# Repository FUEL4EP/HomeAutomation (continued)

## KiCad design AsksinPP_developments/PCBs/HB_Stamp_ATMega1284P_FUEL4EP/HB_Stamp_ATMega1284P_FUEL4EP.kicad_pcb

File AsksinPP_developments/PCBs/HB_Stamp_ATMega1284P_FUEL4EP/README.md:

# HB_Stamp_ATMega1284P_FUEL4EP  

**kleine Platine für DIY AsksinPP Geräte mit I2C und 3x IO-Pins**
- Platinenmaße 22 mm x 40 mm
- Platinendicke: 0.8 mm (bitte nicht ändern, da Antenne sonst nicht funktioniert)
- I2C-Steckerleistenanschluss für I2C-Module
- 3 weitere IO-Pins anschließbar: PC4, PA5, PB3
- optionaler Hochsetzwandler 1,2V .. 1,5V auf 3,3V mit TI TPS61221 für Betrieb mit 1x Batterie
- Versorgung mit 1x AA-Batterie (1,5V) oder 1x NiMH-Akkumulator (1,2V) möglich
- alternativ Versorgung mit 2x AA Batterien ohne Hochsetzwandler
- [integrierte 868 MHz PCB Antenne](https://www.ti.com/lit/an/swra416/swra416.pdf)
- 10 mm x 10 mm kleines Sendemodul [eByte E07 900MM10S](https://datasheet.lcsc.com/lcsc/2305061757_Chengdu-Ebyte-Elec-Tech-E07-900MM10S_C5844212.pdf) auf Platinenrückseite von Hand verlötet
- SMD TQFP-44 [ATMega1284P](https://ww1.microchip.com/downloads/en/DeviceDoc/doc8059.pdf) mit 128kByte Programmspeicher, 16kByte SRAM, 4kByte EEPROM
	+ ohne externen Quarz, Betrieb mit 8 MHz internem RC-Oszillator
		+ bitte dies unbedingt bei der Programmierung von Fuses berücksichtigen!
- Programmierung und Serial Monitor mittels 2,54 mm Pogo-Pin-Adapter, Anschlüsse sind an der gleichen Stelle auf gegenüberliegenden Platinenseiten
- alle SMD Bausteine sind mit dem JLCPCB SMT Bestückungsservice kostengünstig und qualitativ hochwertig bestückbar
- die JLCPCB Assemblierung des Funkmoduls eByte E07-900MM10S geht nur als sehr teures Standard PCBA, daher wird eine Verlötung von Hand empfohlen

- Bilder der bei JLCPCB gefertigten und assemblierten Prototypplatine V1.2

- das eByte E07 900MM10S Sendemodul muss aus Kostengründen von Hand aufgelötet werden
- - V1.2 der Platine hatte noch falsche I2C-Pullup-Widerstände, die ausgelötet werden mussten
- in der aktuellen Version auf Github ist dieser Fehler behoben
- zusätzlich wurden die Anschlussflächen für den Pogo-Pin_Adapter als Ring ausgeführt, damit die Pogo-Pins besser zu zentrieren sind

## Credits

- mein besonderer Dank geht an papa für [AsksinPP](https://github.com/pa-pa/AskSinPP) und [Jérôme jp112sdl](https://github.com/jp112sdl) für die stete Unterstützung.

## Platine V1.2 wurde bei JLCPCB gefertigt und erfolgreich validiert

- entwickelt mit KiCAD 6.0.11
- V1.2 hatte noch falsche I2C-Pullup-Widerstände, die ausgelötet werden mussten
- in der aktuellen Version der Platine auf Github ist dieser Fehler behoben

## Eigenschaften

- kompletter Datensatz für KiCAD 8 auf Github verfügbar:
    + 'git clone https://github.com/FUEL4EP/HomeAutomation.git' oder als [ZIP-Datei](https://github.com/FUEL4EP/HomeAutomation/archive/refs/heads/master.zip)
    + die Platinendaten sind dann unter 'HomeAutomation/AsksinPP_developments/PCBs/HB_Stamp_ATMega1284P_FUEL4EP' direkt mit KiCAD aufrufbar
- neue Eigenschaften:
    + SMD Bestückung, wo möglich
    + alle SMD Bausteine sind mit dem JLCPCB SMT Bestückungsservice kostengünstig und qualitativ hochwertig bestückbar
    + JLCPCB BOM and CPL Dateien für SMT Service werden [bereitgestellt](./jlcpcb/production_files)
    + die AsksinPP Reset- und Config-Taster sind aus Platzgründen als Platinenjumper ausgeführt. Bitte geeignet kurz überbrücken, z.B. mit einem Schraubendreher

### Benötigte Bauteile:

- bei Anspruchsnahme des SMT Bestückungsservice von JLCPCB ist nur noch das Funkmodul eByte E07-900MM10S von Hand auf die Platinenrückseite zu löten
- die JLCPCB Assemblierung des Funkmoduls eByte E07-900MM10S geht nur als sehr teures Standard PCBA, daher wird eine Verlötung von Hand empfohlen

### Passende AsksinPP Projekte von FUEL4EP
   + z.B. [HB-UNI-Sensor1-THPD-SHT45_BME280](https://github.com/FUEL4EP/HomeAutomation/tree/master/AsksinPP_developments/sketches/HB-UNI-Sensor1-THPD-SHT45_BME280)
   
### Aufbauhinweise

- es wird dringend angeraten, als ersten Schritt der Inbetriebnahme einen Frequenztest durchzuführen. Vorher bitte die Fuses mit avrdude setzen.

## Setzen der Fuses des ATMega1284P Mikrokontrollers

- **nie die Fuses auf einen externen Quarzoszillator / Resonator umschalten!**
- ein passender avrdude Skript zum Lesen und korrekten Setzen der Fuses ist [hier](./avrdude)

## Prüfwerkzeuge

- ein Frequenztest ist [hier](./FreqTest_1284P/)

### Anschluss eines FTDI Debuggers und/oder ISP-Programmiergeräts

- Anschluss über 6-Pin 2,54 mm Pogo-Pin-Adapter auf der Platinenoberseite (FTDI Debugger) bzw. der Platinenunterseite (ISP Programmierer)
- bitte vor Anschluss prüfen, dass die korrekte Platinenseite verwendet wird.
- bitte die Beschriftung beachten und vor dem Anlegen eines Pogo-Pin-Adapters querprüfen!
- den ISP-Programmierer auf 3,3V Programmierspannung einstellen.
- zuerst die Fuses mit avrdude setzen
- Bild des Pogo-Pin_Adapters für den FTDI Debugger:

- Bild des Pogo-Pin_Adapters für den Diamex Prog S2 ISP Programmieradapter:

- gegebenenfalls muss die untere Acrylanpressplatte des Pogo-Pin_Adapters z.B. mit einem Dremel verkleinert werden, damit sie an HB_STAMP_ATMEGA1284P_FUEL4EP angebracht werden kann:

- eine Anleitung zur Nutzung des eine Diamex Prog S2 Programmierers unter Linux ist [hier](https://github.com/FUEL4EP/HomeAutomation/tree/master/AsksinPP_developments/HowTos/ISP%20Programmer/Diamex%20Prog-S2) beschrieben

### Passendes Gehäuse
- ein 3D druckbares Gehäuse ist [hier](./case_HB-UNI-Sensor1-THPD-SHT45_BME280/) zu finden  
- ein parametrisierbares OpenSCAD Modell ist beigefügt

### Hinweise
* Achtung: Kein Überspannungsschutz oder Verpolungsschutz vorhanden
* bei der Nutzung des JLCPCB SMT Bestückungsservice ist darauf zu achten, dass **alle** benötigten SMD Bauteile als im Lager **verfügbar** angezeigt werden. Sonst bitte **NICHT** bestellen!

### KiCAD Plugin
- für die Erzeugung der JLCPCB Produktionsdaten wurde das Plugin [KiCAD JLCPCB tools](https://github.com/bouni/kicad-jlcpcb-tools) verwendet.

## Bestellen von Platinen

- die Platine kann direkt bei JLCPCB bestellt und dort auch assembliert werden
- die notwendigen Produktionsdaten stehen [hier](./jlcpcb/production_files/)
- die folgenden Bauteile müssen [vorab bei JLCPCB bestellt werden](https://jlcpcb.com/help/article/53-what-is-jlcpcb-parts-pre-order-service):
	+ [TI TPS61221DCKT](https://jlcpcb.com/parts/componentSearch?searchTxt=TPS61221) (zur Zeit teuer, ist aber meist billiger als zuerst angegeben)
	+ Murata LQH3NPN4R7MMEL 4.7 uH SMD Induktivität
- die JLCPCB Assemblierung des Funkmoduls eByte E07-900MM10S geht nur als das sehr teure Standard PCBA, daher wird eine Verlötung von Hand empfohlen

## Disclaimer

-   die Nutzung der hier veröffentlichten Inhalte erfolgt vollständig auf eigenes Risiko und ohne jede Gewähr.

## Versionsverlauf

-   V1.0   13. Jan 2024: Initiale Vorabfreigabe
-	V1.1	   15. Jan 2024: Änderung der I2C Stiftbelegung
-	V1.2   21. Jan 2024: Drehen der PogoPin-Anschlüsse; Änderung von LCSC-Nummern für bessere Verfügbarkeit
-	V1.3   08. Feb 2024: Fix der I2C Pull-Up Widerstände
-	L V1.4 14. Feb 2024: Pogo-Pin Pads in Ringform
-	L V1.5 29. Sep 2024: Migration zu KiCAD 8
-	S V1.4 29. Sep 2024: Migration zu KiCAD 8
- 	KiCad Schaltplan-Editor   Version: 8.0.5-8.0.5-0~ubuntu22.04.1, release build unter Kubuntu22.04.1
- 	KiCad Leiterplatteneditor Version: 8.0.5-8.0.5-0~ubuntu22.04.1, release build unter Kubuntu22.04.1
- 	PCB Version 1.5
- 	Schematics  1.4

## Lizenz 

**Creative Commons BY-NC-SA**<br>
Give Credit, NonCommercial, ShareAlike

<br />This work is licensed under a <a rel="license" href="http://creativecommons.org/licenses/by-nc-sa/4.0/">Creative Commons Attribution-NonCommercial-ShareAlike 4.0 International License</a>.

-EOF

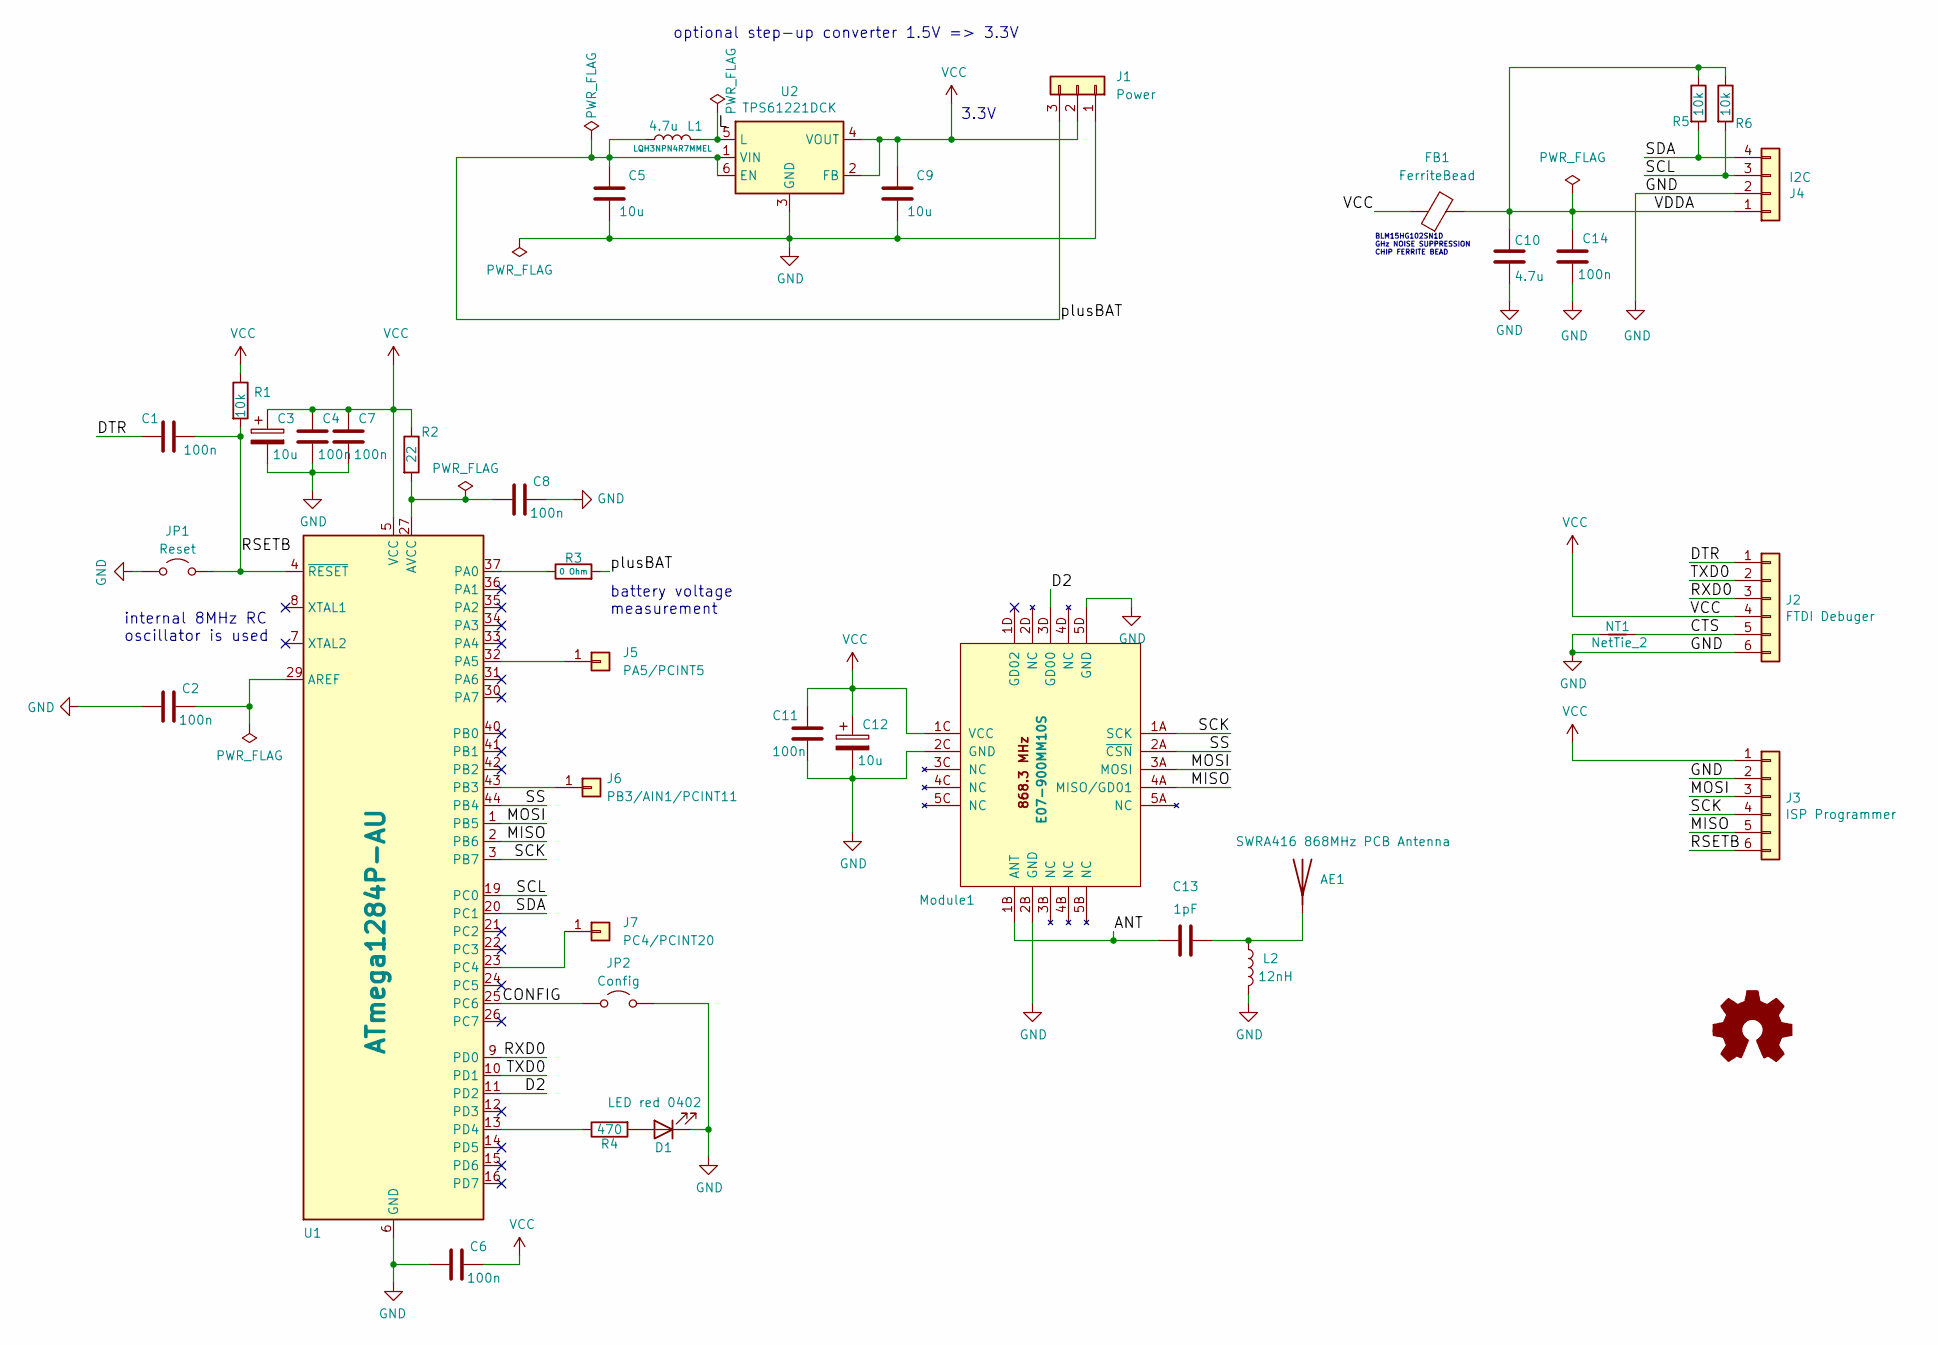
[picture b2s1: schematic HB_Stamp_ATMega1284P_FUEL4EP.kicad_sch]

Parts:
AE1: SWRA416 868MHz PCB Antenna; Texas_SWRA416_868MHz_915MHz
C1, C2, C4, C6, C7, C8, C11, C14: 100n; C_0402_1005Metric; LCSC C1525
C3, C12: 10u; C_0402_1005Metric; LCSC C15525
C5, C9: 10u; C_0805_2012Metric; LCSC C15850
C10: 4.7u; C_0402_1005Metric; LCSC C23733
C13: 1pF; C_0402_1005Metric; LCSC C72134
D1: LED red 0402; LED_0402_1005Metric; LCSC C273598
FB1: FerriteBead; L_0402_1005Metric; LCSC C76889
J1: Power; PinHeader_1x03_P2.54mm_Vertical
J2: FTDI Debuger; PogoPinHeader_SMD_1x06_P2.54mm_Vertical
J3: ISP Programmer; PogoPinHeader_SMD_1x06_P2.54mm_Vertical
J4: I2C; PinHeader_1x04_P2.54mm_Vertical
J5: PA5/PCINT5; PinHeader_1x01_P2.54mm_Vertical
J6: PB3/AIN1/PCINT11; TestPoint_Pad_1.0x1.0mm
J7: PC4/PCINT20; PinHeader_1x01_P2.54mm_Vertical
JP1: Reset; SolderJumper-2_P1.3mm_Open_Pad1.0x1.5mm
JP2: Config; SolderJumper-2_P1.3mm_Open_Pad1.0x1.5mm
L1: 4.7u; FUEL4EP_Inductor_SMD_1; LCSC C576538
L2: 12nH; L_0402_1005Metric; LCSC C2043991
LOGO1: Logo_Open_Hardware_Small; CC-BY-ND-SA
Module1: E07-900MM10S; eByte_E07-900MM10S; LCSC C5844212
NT1: NetTie_2; NetTie-2_SMD_Pad0.5mm
R1, R5, R6: 10k; R_0402_1005Metric; LCSC C25744
R2: 22; R_0402_1005Metric; LCSC C23345
R3: 0 Ohm; R_0402_1005Metric; LCSC C17168
R4: 470; R_0402_1005Metric; LCSC C25117
U1: ATmega1284P-AU; TQFP-44_10x10mm_P0.8mm; LCSC C33575
U2: TPS61221DCK; Texas_R-PDSO-G6; LCSC C2865756

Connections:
/ANT: C13.1, Module1.1B (ANT)
/CONFIG: JP2.1 (A), U1.25 (PC6)
/CTS: J2.5, NT1.2
/D2: Module1.3D (GD00), U1.11 (PD2)
/DTR: C1.1, J2.1
/L: L1.2, U2.5 (L)
/MISO: J3.5, Module1.4A (MISO/GD01), U1.2 (PB6)
/MOSI: J3.3, Module1.3A (MOSI), U1.1 (PB5)
/RSETB: C1.2, J3.6, JP1.2 (B), R1.2, U1.4 (~RESET)
/RXD0: J2.3, U1.9 (PD0)
/SCK: J3.4, Module1.1A (SCK), U1.3 (PB7)
/SCL: J4.3, R6.2, U1.19 (PC0)
/SDA: J4.4, R5.2, U1.20 (PC1)
/SS: Module1.2A (~CSN), U1.44 (PB4)
/TXD0: J2.2, U1.10 (PD1)
/VDDA: C10.1, C14.1, FB1.2, J4.1, R5.1, R6.1
/plusBAT: C5.1, J1.3, L1.1, R3.2, U2.1 (VIN), U2.6 (EN)
GND: C2.1, C3.2, C4.2, C5.2, C6.1, C7.2, C8.2, C9.2, C10.2, C11.2, C12.2, C14.2, D1.1 (K), J1.1, J2.6, J3.2, J4.2, JP1.1 (A), JP2.2 (B), L2.2, Module1.2B (GND), Module1.2C (GND), Module1.5D (GND), NT1.1, U1.6 (GND), U1.18 (GND), U1.28 (GND), U1.39 (GND), U2.3 (GND)
unnamed: AE1.1 (A), C13.2, L2.1
unnamed: D1.2 (A), R4.2
unnamed: J5.1, U1.32 (PA5)
unnamed: J6.1, U1.43 (PB3)
unnamed: J7.1, U1.23 (PC4)
unnamed: C2.2, U1.29 (AREF)
unnamed: C8.1, R2.2, U1.27 (AVCC)
unnamed: R3.1, U1.37 (PA0)
unnamed: R4.1, U1.13 (PD4)
VCC: C3.1, C4.1, C6.2, C7.1, C9.1, C11.1, C12.1, FB1.1, J1.2, J2.4, J3.1, Module1.1C (VCC), R1.1, R2.1, U1.5 (VCC), U1.17 (VCC), U1.38 (VCC), U2.2 (FB), U2.4 (VOUT)

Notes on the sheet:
battery voltage measurement
internal 8MHz RC oscillator is used
BLM15HG102SN1D GHz NOISE SUPPRESSION CHIP FERRITE BEAD
3.3V
optional step-up converter 1.5V => 3.3V

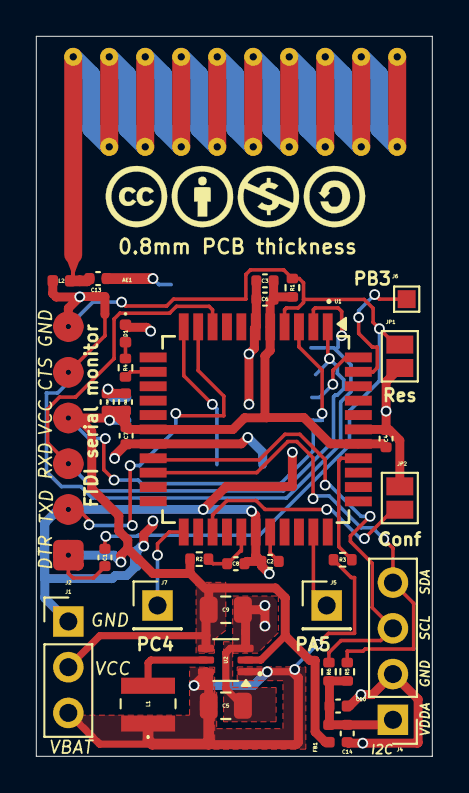
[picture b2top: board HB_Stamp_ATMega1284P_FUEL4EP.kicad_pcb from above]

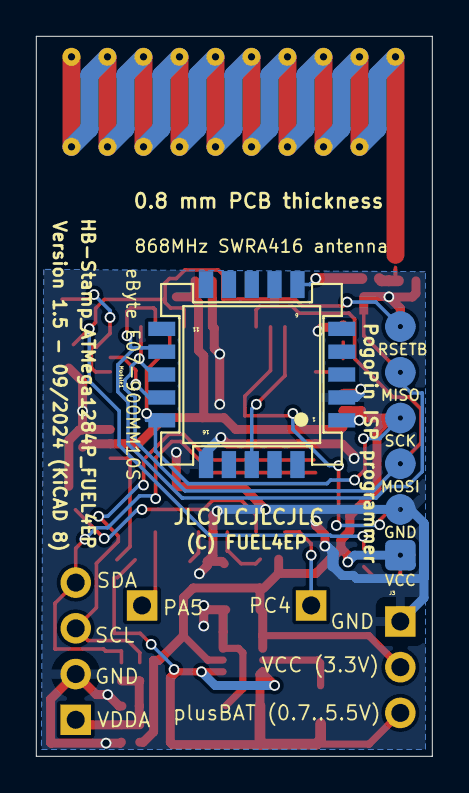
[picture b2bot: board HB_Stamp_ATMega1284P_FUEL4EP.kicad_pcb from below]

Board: 2 copper layers, 22.0 x 40.0 mm, 39 parts (2 on the bottom side), 28 nets.

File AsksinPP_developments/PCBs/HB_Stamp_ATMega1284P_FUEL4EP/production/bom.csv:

Designator,Footprint,Quantity,Value,LCSC Part #
AE1,Texas_SWRA416_868MHz_915MHz,1,SWRA416 868MHz PCB Antenna,
"C1, C11, C14, C2, C4, C6, C7, C8",0402,8,100n,C1525
C10,0402,1,4.7u,C23733
"C12, C3",0402,2,10u,C15525
C13,0402,1,1pF,C72134
"C5, C9",0805,2,10u,C15850
D1,0402,1,LED red 0402,C273598
FB1,0402,1,FerriteBead,C76889
J1,PinHeader_1x03_P2.54mm_Vertical,1,Power,
J2,PogoPinHeader_SMD_1x06_P2.54mm_Vertical,1,FTDI Debuger,
J3,PogoPinHeader_SMD_1x06_P2.54mm_Vertical,1,ISP Programmer,
J4,PinHeader_1x04_P2.54mm_Vertical,1,I2C,
J5,PinHeader_1x01_P2.54mm_Vertical,1,PA5/PCINT5,
J6,TestPoint_Pad_1.0x1.0mm,1,PB3/AIN1/PCINT11,
J7,PinHeader_1x01_P2.54mm_Vertical,1,PC4/PCINT20,
JP1,SolderJumper-2_P1.3mm_Open_Pad1.0x1.5mm,1,Reset,
JP2,SolderJumper-2_P1.3mm_Open_Pad1.0x1.5mm,1,Config,
L1,FUEL4EP_Inductor_SMD_1,1,4.7u,C576538
L2,0402,1,12nH,C2043991
Module1,eByte_E07-900MM10S,1,E07-900MM10S,C5844212
"R1, R5, R6",0402,3,10k,C25744
R2,0402,1,22,C23345
R3,0402,1,0 Ohm,C17168
R4,0402,1,470,C25117
U1,TQFP-44_10x10mm_P0.8mm,1,ATmega1284P-AU,C33575
U2,Texas_R-PDSO-G6,1,TPS61221DCK,C2865756

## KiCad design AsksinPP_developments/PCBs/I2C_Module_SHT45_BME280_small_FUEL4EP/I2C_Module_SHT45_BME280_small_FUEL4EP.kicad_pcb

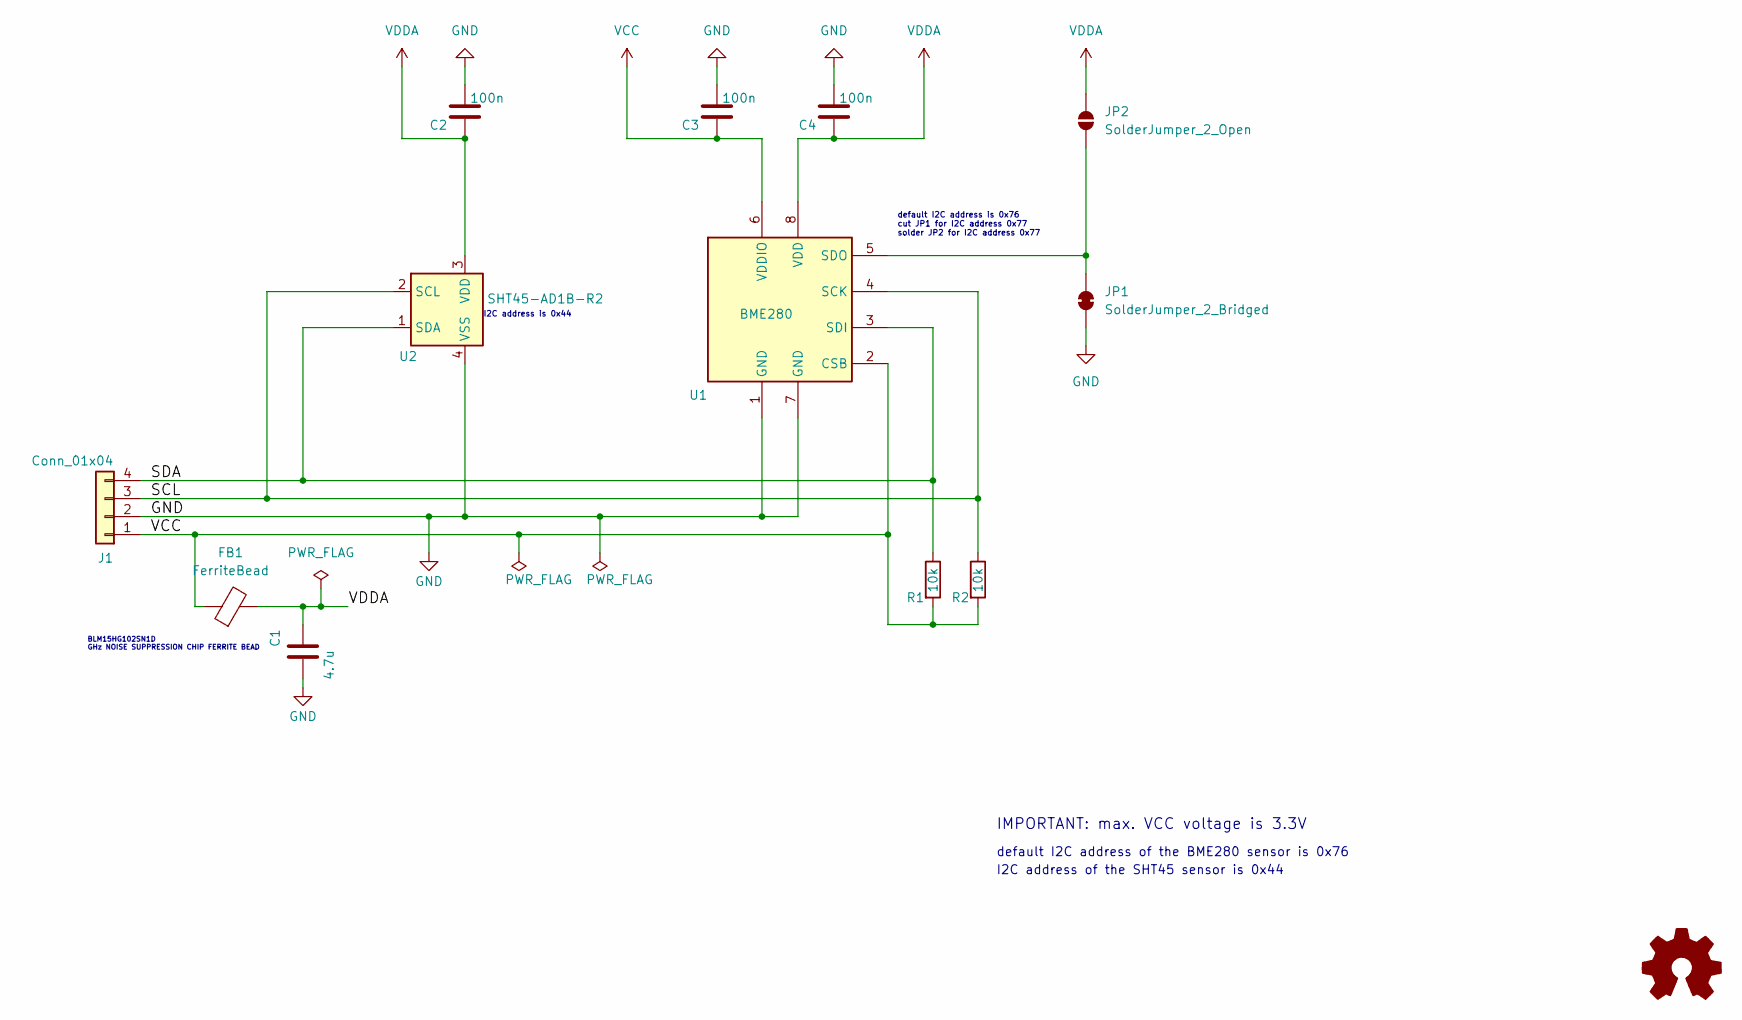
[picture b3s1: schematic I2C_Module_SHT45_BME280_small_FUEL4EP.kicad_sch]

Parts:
C1: 4.7u; C_0603_1608Metric; LCSC C19666
C2, C3, C4: 100n; C_0603_1608Metric; LCSC C14663
FB1: FerriteBead; L_0402_1005Metric; LCSC C76889
J1: Conn_01x04; PinHeader_1x04_P2.54mm_Vertical
JP1: SolderJumper_2_Bridged; SolderJumper-2_P1.3mm_Bridged_Pad1.0x1.5mm
JP2: SolderJumper_2_Open; SolderJumper-2_P1.3mm_Open_Pad1.0x1.5mm
LOGO1: Logo_Open_Hardware_Small; CC-BY-ND-SA
R1, R2: 10k; R_0402_1005Metric; LCSC C25744
U1: BME280; Bosch_LGA-8_2.5x2.5mm_P0.65mm_ClockwisePinNumbering; LCSC C92489
U2: SHT45-AD1B-R2; Sensirion_DFN-4_1.5x1.5mm_P0.8mm_SHT4x_NoCentralPad; LCSC C5221601

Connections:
/SCL: J1.3, R2.1, U1.4 (SCK), U2.2 (SCL)
/SDA: J1.4, R1.1, U1.3 (SDI), U2.1 (SDA)
GND: C1.2, C2.1, C3.1, C4.1, J1.2, JP1.1 (A), U1.1 (GND), U1.7 (GND), U2.4 (VSS)
unnamed: JP1.2 (B), JP2.1 (A), U1.5 (SDO)
VCC: C3.2, FB1.1, J1.1, R1.2, R2.2, U1.2 (CSB), U1.6 (VDDIO)
VDDA: C1.1, C2.2, C4.2, FB1.2, JP2.2 (B), U1.8 (VDD), U2.3 (VDD)

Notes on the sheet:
cut JP1 for I2C address 0x77
I2C address is 0x44
BLM15HG102SN1D GHz NOISE SUPPRESSION CHIP FERRITE BEAD
solder JP2 for I2C address 0x77
default I2C address of the BME280 sensor is 0x76
I2C address of the SHT45 sensor is 0x44
default I2C address is 0x76
IMPORTANT: max. VCC voltage is 3.3V

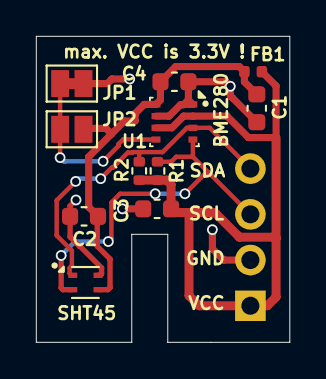
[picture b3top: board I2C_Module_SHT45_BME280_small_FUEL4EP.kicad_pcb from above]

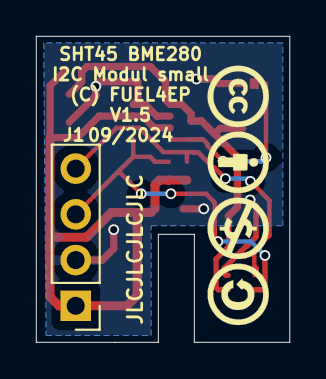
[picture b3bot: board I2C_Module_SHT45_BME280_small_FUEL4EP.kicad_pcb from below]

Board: 2 copper layers, 14.1 x 17.0 mm, 13 parts (2 on the bottom side), 6 nets.

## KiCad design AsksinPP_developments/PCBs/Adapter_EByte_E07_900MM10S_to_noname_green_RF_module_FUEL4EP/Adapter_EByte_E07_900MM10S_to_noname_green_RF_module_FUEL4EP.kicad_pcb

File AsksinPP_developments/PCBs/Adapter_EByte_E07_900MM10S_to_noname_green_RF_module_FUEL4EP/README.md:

# Adapter_EByte_E07_900MM10S_to_noname_green_RF_module_FUEL4EP  

## Ersatz für das NoName grüne 868,3 MHz Funkmodul

- Da das NoName grüne 868,3 MHz Modul häufig eine schlechte Qualität hat, wurde dieser Adapter als Ersatz entworfen. Es wird ein verfügbares, qualitativ hochwertiges EByte E07 900MM10S Funkmodul mit Abschirmkappe verbaut.

## Adapter für 868,3 MHz Funkmodul Ebyte E07 900MM10S auf das NoName grüne 868,3 MHz Funkmodul

- Infos zu AsksinPP sind [hier](https://asksinpp.de) und [hier](https://asksinpp.de/Grundlagen/01_hardware.html#verdrahtung) zu finden

## Umbenennung

- der PCB Name wurde in Version 1.1 von 'Adapter_noname_green_RF_module_to_Ebyte_E07_868MS10_FUEL4EP' in 'Adapter_EByte_E07_900MM10S_to_noname_green_RF_module_FUEL4EP' umbenannt

## Platinenmaße

- Breite: 19,2 mm
- Weite: 17 mm

## Stromlaufplan

- ist [hier](./Schematics/Adapter_EByte_E07_900MM10S_to_noname_green_RF_module_FUEL4EP.pdf)

## Status

- die Platine V1.0 wurde bei JLCPCB gefertigt und ist von Hand bestückt und verlötet worden
- die Platine V1.0 wurde am 07.  Mai 2025 erfolgreich mit dem Sketch [HB-UNI-Sensor1-THPD-SHT45_BME280](https://github.com/FUEL4EP/HomeAutomation/tree/master/AsksinPP_developments/sketches/HB-UNI-Sensor1-THPD-SHT45_BME280) validiert:
 
- Bilder der gefertigten Prototypen V1.0 (noch mit altem PCB-Namen):
- 

## Rückmeldungen

- sind willkommen.

## Daten für die Bestellung bei JLCPCB

- die Daten für die Bestellung liegen im Verzeichnis [./jlcpcb/production_files/](./jlcpcb/production_files/)
- Gerber-Daten als Zip-Datei
- BOM- und CPL-Daten als CSV-Datei

## Hinweis für Bestückung bei JLCPCB

- bei der Bestellung bitte angeben '[specify a location](https://jlcpcb.com/help/article/50-How-to-remove-order-number-from-your-PCB)'

- der  Dummy-Text 'JLCJLCJLCJLC' ist auf der Rückseite der Platine

- Bestückung des Funkmoduls Ebyte E07 900MM10S geht bei JLCPCB nur als teures Standard-PCBA. Daher löte ich das Funkmodul immer von Hand auf.

## Hinweis für Bestückung von Hand

- die Ferritperle FB1 (0603) kann entweder mit
	+ Murata EMI Suppression Filter SMD0603 BLM18 470 Ohm, erhältlich z.B.  bei Reichelt als Bestellnummer [BLM18AG 471](https://www.reichelt.de/de/de/shop/produkt/emi_suppression_filter_smd0603_blm18_470_ohm-89677)
- oder bei geringeren Anforderungen an Störunterdrückung mit Lötzinn überbrückt werden

## lokale Installation des Github Releases auf Deinem Computer

- gehe bitte in Dein Zielinstallationsverzeichnis, wo Du mit der Adapter_EByte_E07_900MM10S_to_noname_green_RF_module_FUEL4EP Platine mit KiCAD arbeiten möchtest

  - gebe dort 'git clone https://github.com/FUEL4EP/HomeAutomation.git' ein
	  + damit lädst Du mein [Sammelrepository](https://github.com/FUEL4EP/HomeAutomation) für alle meine auf Github freigegebenen HomeBrew Entwicklungen herunter.
  - dann findest Du ein neues Verzeichnis 'HomeAutomation' auf Deinem Rechner, das alle meine auf Github freigebenen Entwicklungen enthält, siehe [README.md](https://github.com/FUEL4EP/HomeAutomation/blob/master/README.md)
  	+ mache bitte regelmäßig ein Update mit 'git pull'
 -	die Platine Adapter_EByte_E07_900MM10S_to_noname_green_RF_module_FUEL4EP findest Du unter './HomeAutomation/tree/master/AsksinPP_developments/PCBs/Adapter_EByte_E07_900MM10S_to_noname_green_RF_module_FUEL4EP'
 
- alternativ kann vom Github [Sammelrepository](https://github.com/FUEL4EP/HomeAutomation) die ZIP-Datei HomeAutomation-master.zip heruntergeladen und auf dem lokalen Rechner ausgepackt werden. Bitte dann regelmäßig auf Github nach Updates schauen.

## Versionsverlauf

-   V1.0 18. Apr 2025: Initiale Version
-   V1.1 07. Mai 2025: Änderung des PCB Namens auf 'Adapter_EByte_E07_900MM10S_to_noname_green_RF_module_FUEL4EP' 
- KiCad Schaltplan-Editor Version: 8.0.5-8.0.5-0~ubuntu22.04.1 unter Kubuntu22.04.1
- KiCad Leiterplatteneditor Version: 8.0.5-8.0.5-0~ubuntu22.04.1 unter Kubuntu22.04.1
- PCB Version 1.1
- Schematics  1.1

## Disclaimer

-   die Nutzung der hier veröffentlichten Inhalte erfolgt vollständig auf eigenes Risiko und ohne jede Gewähr.
-  der Nutzer dieser Platine ist selbst dafür verantwortlich, dass die relevanten Richtlinien für Funkanlagen, z.B. in der EU die Funkanlagenrichtlinie (2014/53/EU, auch bekannt als RED), eingehalten wird.

## Lizenz 

**Creative Commons BY-NC-SA**<br>
Give Credit, NonCommercial, ShareAlike

<br />This work is licensed under a <a rel="license" href="http://creativecommons.org/licenses/by-nc-sa/4.0/">Creative Commons Attribution-NonCommercial-ShareAlike 4.0 International License</a>.

-EOF

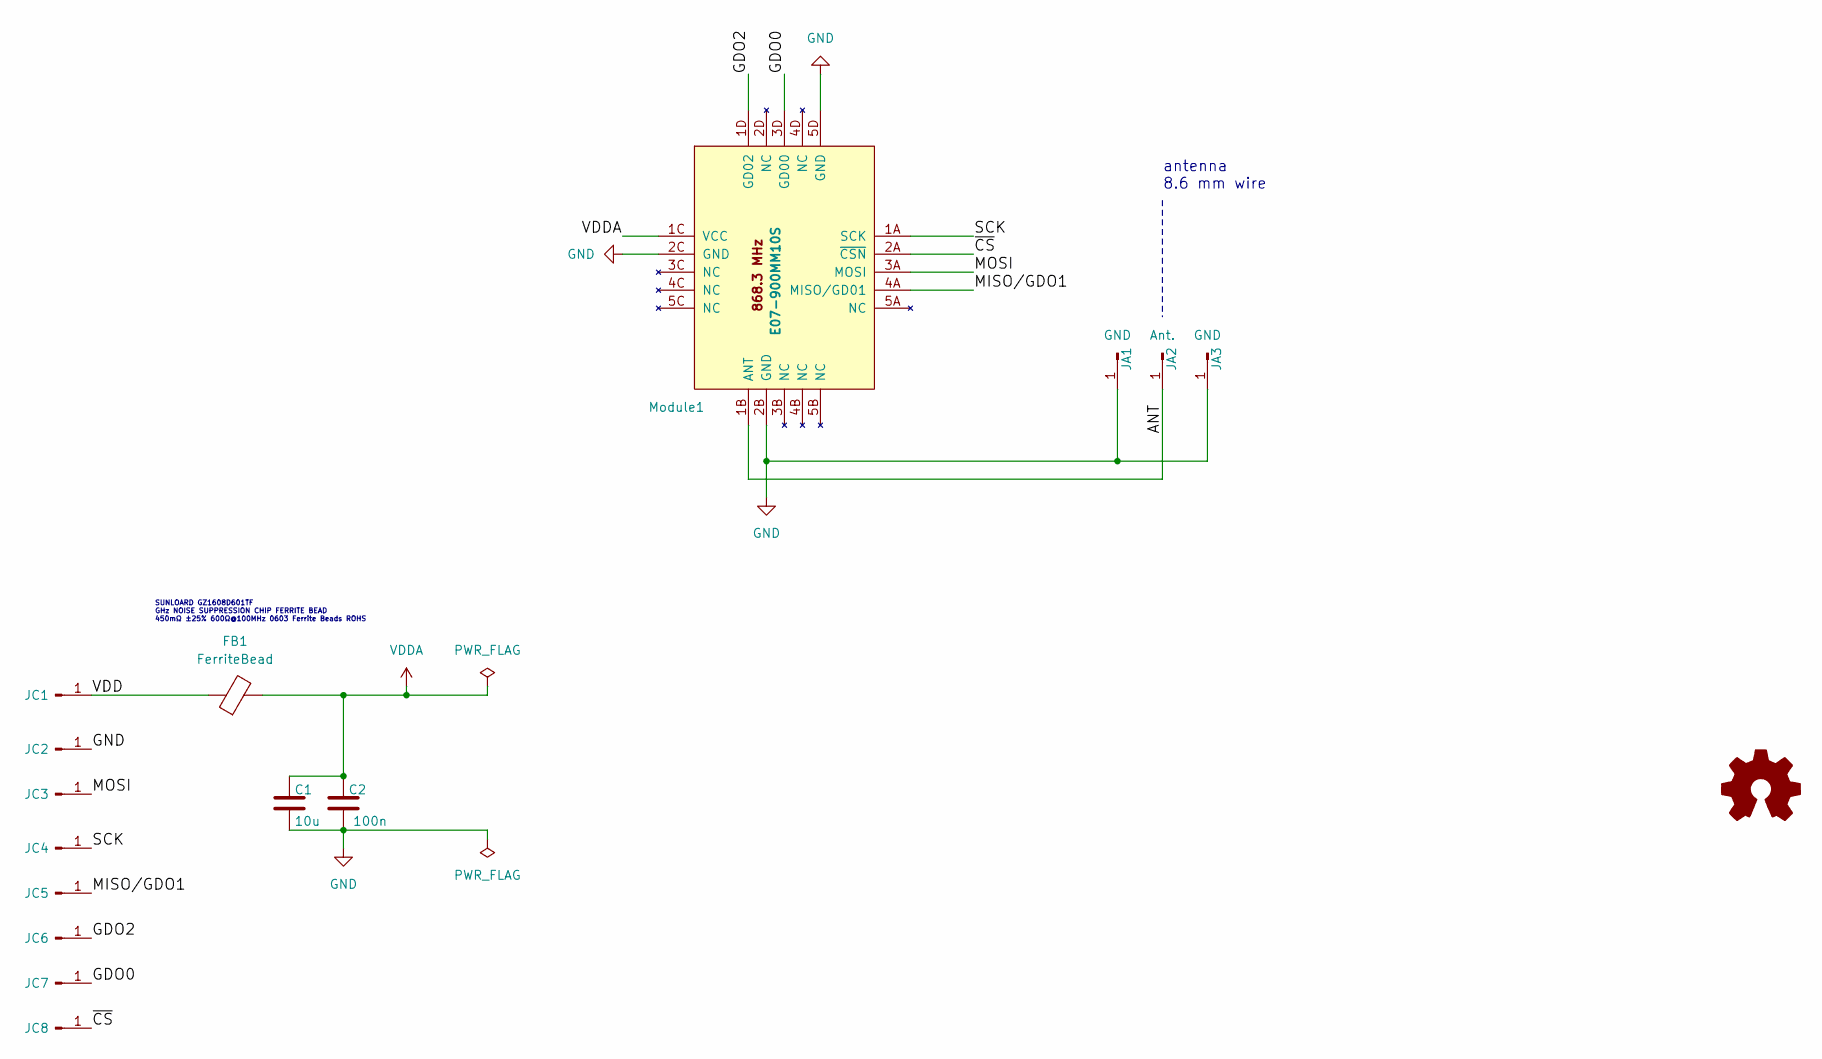
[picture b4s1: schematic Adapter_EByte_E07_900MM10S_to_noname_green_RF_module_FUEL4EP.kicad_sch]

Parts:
C1: 10u; C_0603_1608Metric; LCSC C19702
C2: 100n; C_0603_1608Metric; LCSC C14663
FB1: FerriteBead; L_0603_1608Metric; LCSC C1002
JA1, JA3: GND; hole_Pitch2.54mm_Drill0.9mm
JA2: Ant.; hole_Pitch2.54mm_Drill0.9mm
JC1: Conn_01x01_Pin; hole_Pitch2.00mm_Drill0.8mm
JC2, JC3, JC4, JC5, JC6, JC7, JC8: Conn_01x01_Pin; hole_Pitch2.00mm_Drill0.8mm_rounded
LOGO1: Logo_Open_Hardware_Small; CC-BY-ND-SA_bottom
Module1: E07-900MM10S; eByte_E07-900MM10S; LCSC C5844212

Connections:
/ANT: JA2.1, Module1.1B (ANT)
/GDO0: JC7.1, Module1.3D (GD00)
/GDO2: JC6.1, Module1.1D (GD02)
/MISO/GDO1: JC5.1, Module1.4A (MISO/GD01)
/MOSI: JC3.1, Module1.3A (MOSI)
/SCK: JC4.1, Module1.1A (SCK)
/VDD: FB1.1, JC1.1
/~CS: JC8.1, Module1.2A (~CSN)
GND: C1.2, C2.2, JA1.1, JA3.1, JC2.1, Module1.2B (GND), Module1.2C (GND), Module1.5D (GND)
VDDA: C1.1, C2.1, FB1.2, Module1.1C (VCC)

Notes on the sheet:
SUNLOARD GZ1608D601TF GHz NOISE SUPPRESSION CHIP FERRITE BEAD 450mΩ ±25% 600Ω@100MHz 0603 Ferrite Beads ROHS
antenna 8.6 mm wire

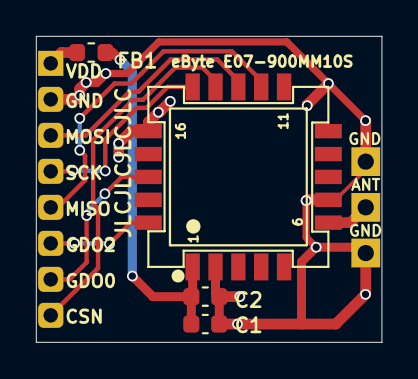
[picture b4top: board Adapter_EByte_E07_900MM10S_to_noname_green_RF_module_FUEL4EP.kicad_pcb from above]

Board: 2 copper layers, 19.2 x 17.0 mm, 16 parts (0 on the bottom side), 10 nets.

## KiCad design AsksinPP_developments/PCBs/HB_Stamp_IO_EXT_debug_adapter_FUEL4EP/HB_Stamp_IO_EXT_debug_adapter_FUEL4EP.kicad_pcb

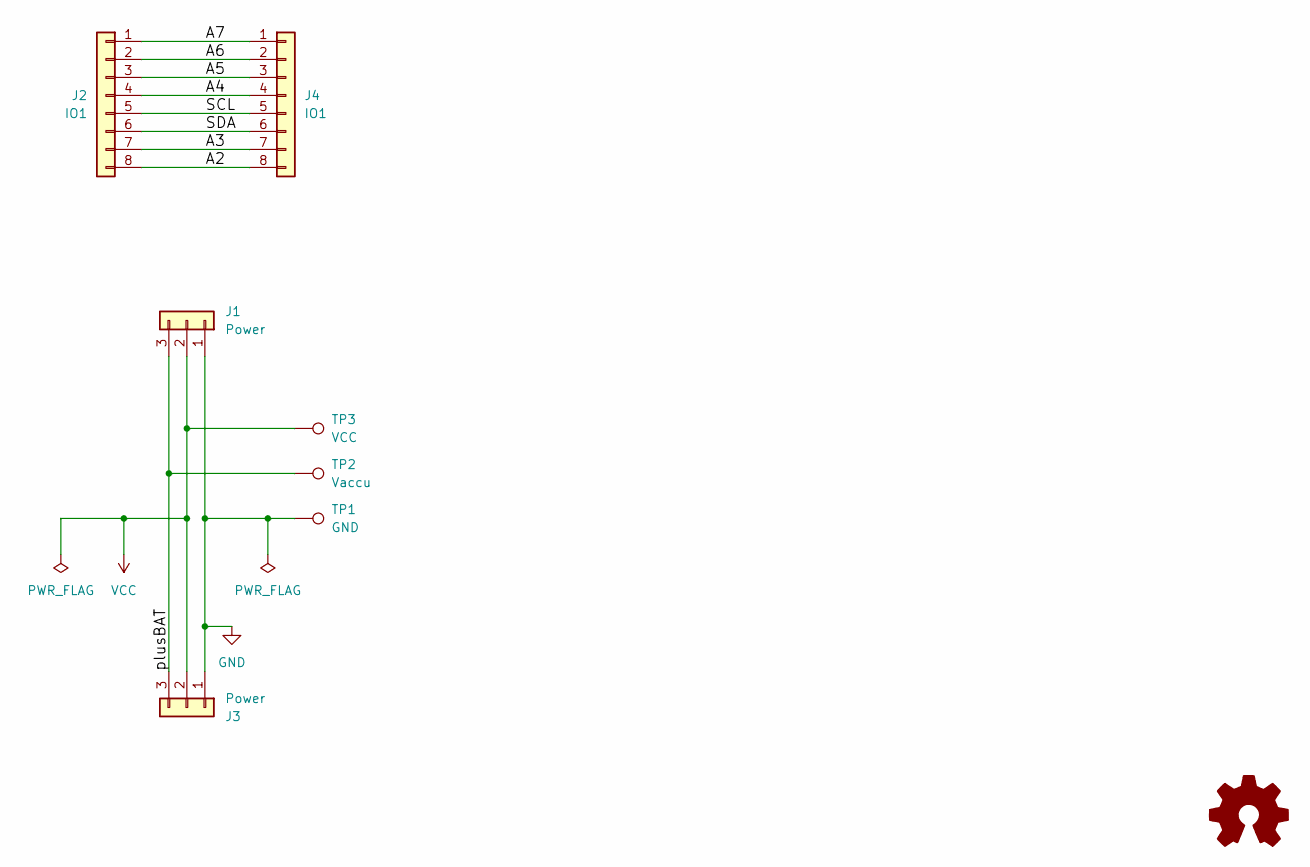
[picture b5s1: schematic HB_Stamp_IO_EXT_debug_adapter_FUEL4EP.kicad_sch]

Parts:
J1, J3: Power; PinHeader_1x03_P1.27mm_Vertical
J2, J4: IO1; PinHeader_1x08_P1.27mm_Vertical
LOGO1: Logo_Open_Hardware_Small; CC-BY-ND-SA_bottom
TP1: GND; TestPoint_Pad_1.0x1.0mm
TP2: Vaccu; TestPoint_Pad_1.0x1.0mm
TP3: VCC; TestPoint_Pad_1.0x1.0mm

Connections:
/A2: J2.8, J4.8
/A3: J2.7, J4.7
/A4: J2.4, J4.4
/A5: J2.3, J4.3
/A6: J2.2, J4.2
/A7: J2.1, J4.1
/SCL: J2.5, J4.5
/SDA: J2.6, J4.6
/plusBAT: J1.3, J3.3, TP2.1
GND: J1.1, J3.1, TP1.1
VCC: J1.2, J3.2, TP3.1

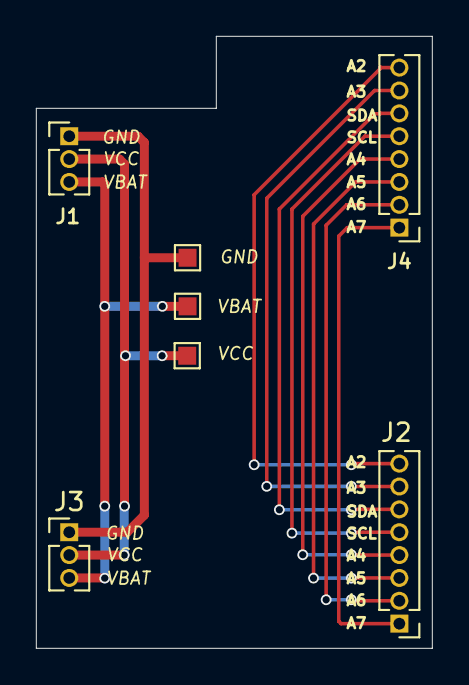
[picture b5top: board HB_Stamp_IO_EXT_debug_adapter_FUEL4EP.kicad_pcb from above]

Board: 2 copper layers, 22.0 x 34.0 mm, 8 parts (0 on the bottom side), 11 nets.
